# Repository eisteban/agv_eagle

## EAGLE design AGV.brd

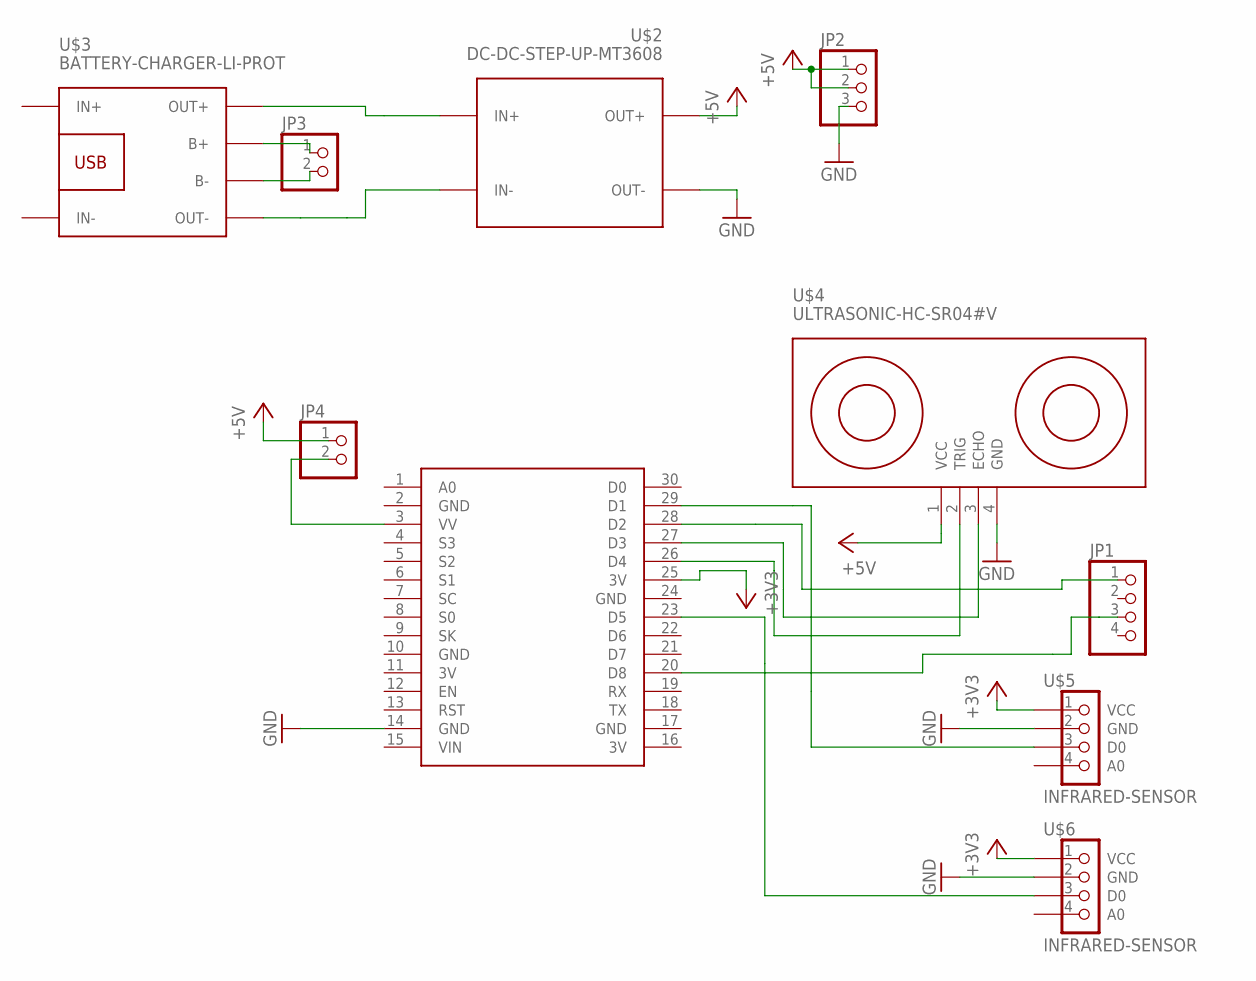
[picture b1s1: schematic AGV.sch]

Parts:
JP1: PINHD-1X4; 1X04
JP2: PINHD-1X3; 1X03
JP3, JP4: PINHD-1X2; 1X02
U$1: NODEMCU
U$2: DC-DC-STEP-UP-MT3608
U$3: BATTERY-CHARGER-LI-PROT
U$4: ULTRASONIC-HC-SR04#V
U$5, U$6: INFRARED-SENSOR

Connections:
3V: U$1.11 (3V), U$1.16 (3V)
+3V3: U$1.25 (3V), U$5.1 (VCC), U$6.1 (VCC)
+5V: JP2.1, JP2.2, JP4.1, U$2.OUT+, U$4.1 (VCC)
GND: JP2.3, U$1.2 (GND), U$1.10 (GND), U$1.14 (GND), U$1.17 (GND), U$1.24 (GND), U$2.OUT-, U$4.4 (GND), U$5.2 (GND), U$6.2 (GND)
unnamed: JP3.1, U$3.B+
unnamed: JP3.2, U$3.B-
unnamed: U$2.IN+, U$3.OUT+
unnamed: U$2.IN-, U$3.OUT-
unnamed: U$1.29 (D1), U$5.3 (D0)
unnamed: JP1.1, U$1.28 (D2)
unnamed: U$1.27 (D3), U$4.3 (ECHO)
unnamed: U$1.26 (D4), U$4.2 (TRIG)
unnamed: JP4.2, U$1.3 (VV)
unnamed: U$1.23 (D5), U$6.3 (D0)
unnamed: JP1.3, U$1.20 (D8)

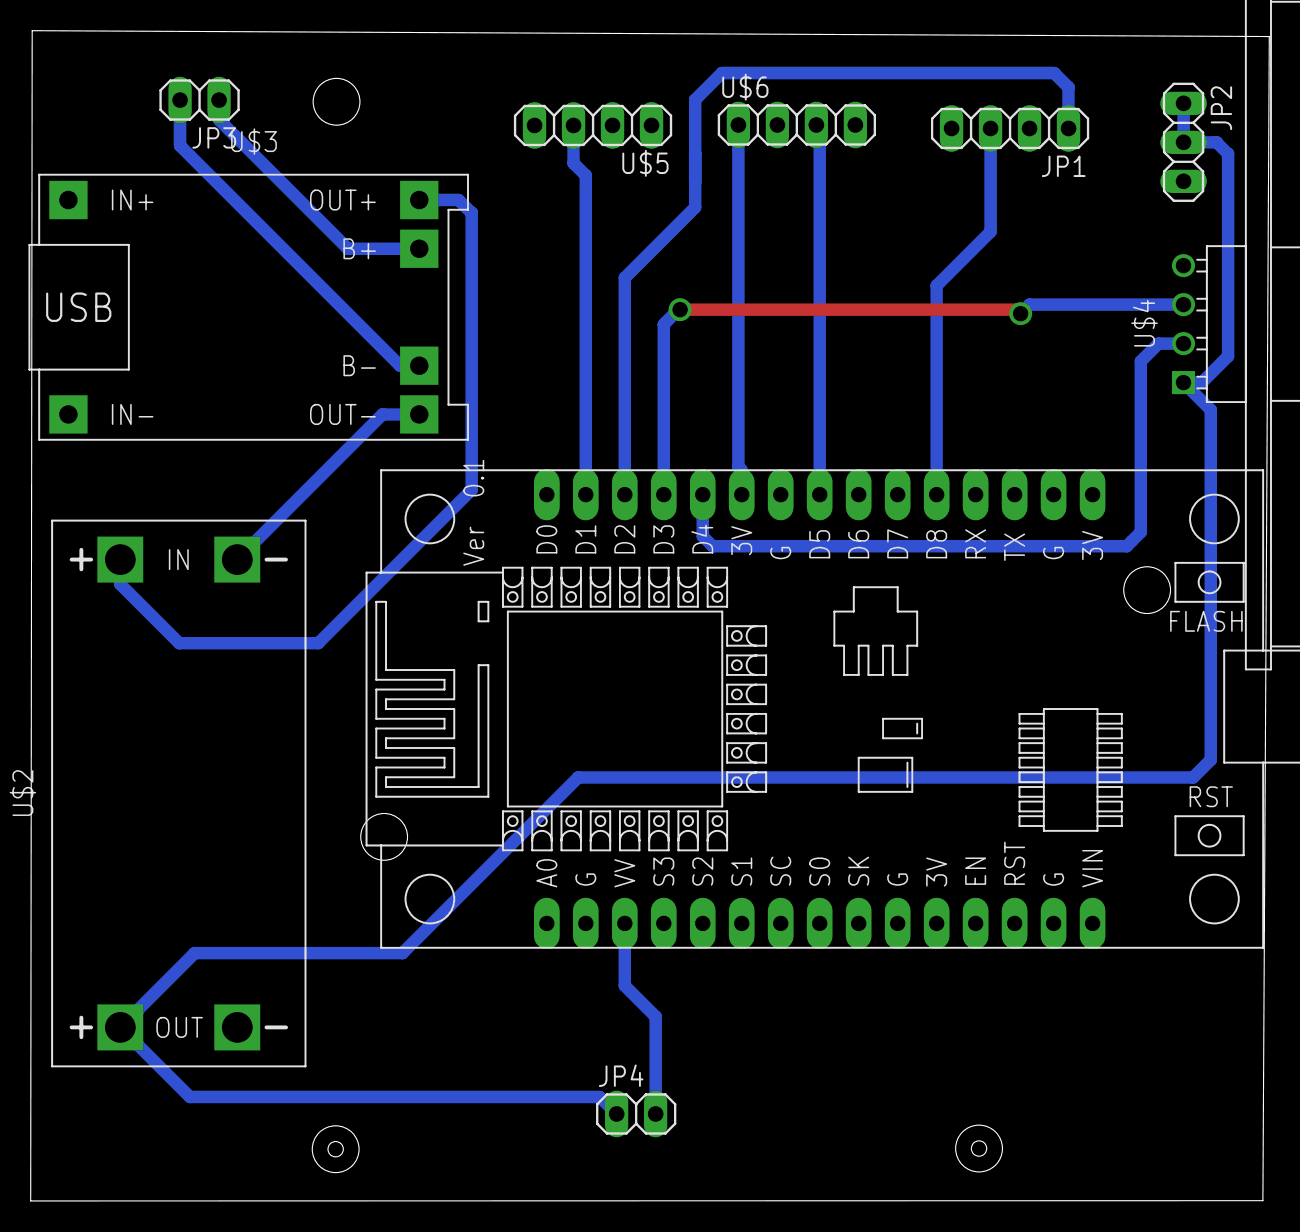
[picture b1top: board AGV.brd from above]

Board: 2 copper layers, 80.7 x 76.3 mm, 10 parts (0 on the bottom side), 15 nets.

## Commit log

2019-12-05 Primer commit
2019-12-06 reubicación de orificios para tornillos

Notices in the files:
parts and their libraries:
DIY Modules: Released under the Creative Commons Attribution 4.0 International License: http://creativecommons.org/licenses/by/4.0
